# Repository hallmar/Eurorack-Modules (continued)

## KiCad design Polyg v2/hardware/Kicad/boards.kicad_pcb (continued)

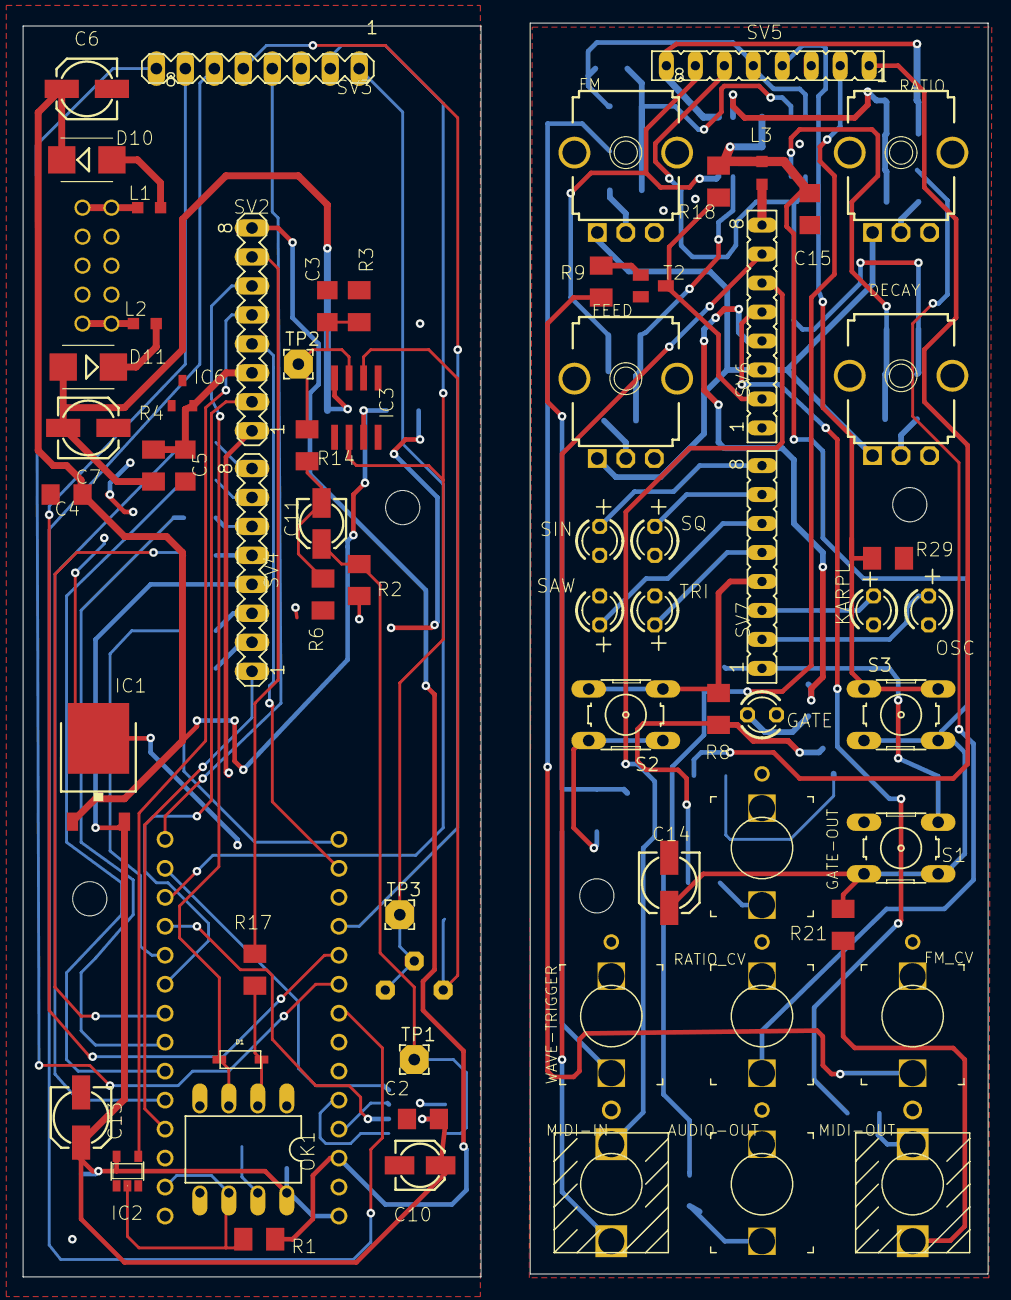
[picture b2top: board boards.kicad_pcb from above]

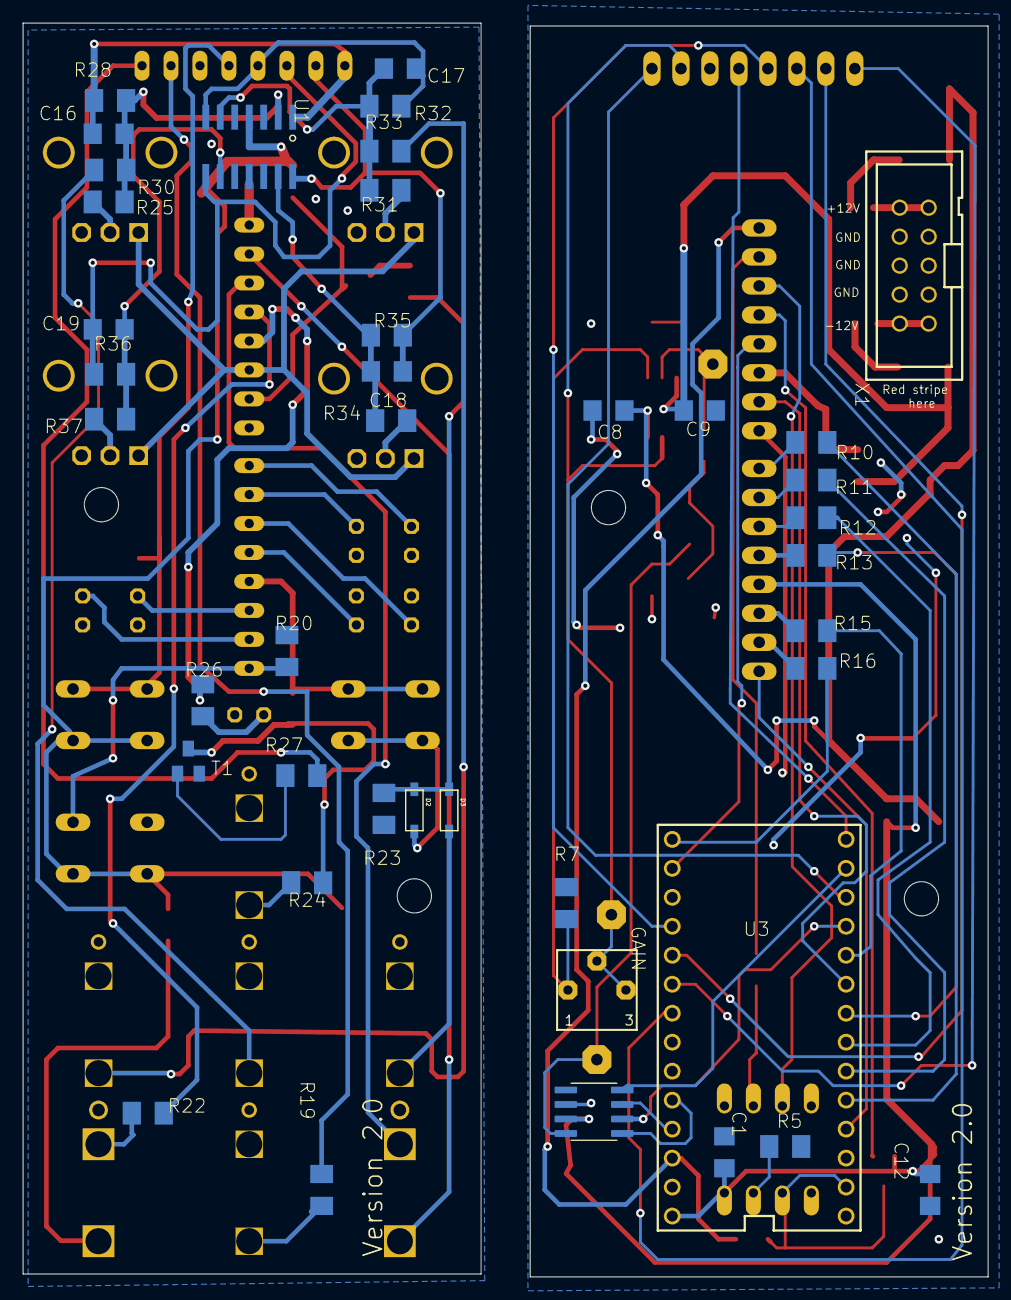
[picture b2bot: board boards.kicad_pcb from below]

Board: 2 copper layers, 84.6 x 109.9 mm, 110 parts (41 on the bottom side), 91 nets.

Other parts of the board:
@HOLE0, @HOLE1, @HOLE2, @HOLE3: (no value)

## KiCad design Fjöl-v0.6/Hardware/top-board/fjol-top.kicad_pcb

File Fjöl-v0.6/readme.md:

# Fjöl 4-Voice Midi synth, THIS IS A DEPRECATED PROJECT AND I'M ONLY KEEPING THIS HERE FOR ARCHIVING PURPOSES

Small demo video with non working LED's: https://www.youtube.com/watch?v=nTqA_WNiwQo

Current hardware uses a high quality DAC(PCM5100) with 16bit/44.1kHz quality.

Fjöl is a 
4 voice polyphonic* Phase modulation synthesizer. Using only sine waves you can get the same sounds as an FM synthesizer.

* digital ladder LPF with resonance
* usb A host
* 3 operator Phase modulation with 3 algorithms(so far)
* two endless encoders with CV input for adjusting 8 different parameters 
* MIDI IN and MIDI THRU with type A midi minijacks as per MIDI standard.
* optional V/OCT and gate per voice expander also in the works
* i2c compatibility with Monome Teletype and Monome Crow (using Just Friends commands) is also on the roadmap
* possible Monome Grid compatibility on the roadmap

*(technically paraphonic since it's one filter for all voices)

Encoder parameters are:

* stereo spread of voices
* filter resonance
* filter envelope decay
* glide/portamento
* Operator 2 detune
* Operator 3 detune
* Operator 1 feedback (creates saw like wave)
* Operator 2 feedback

Potentiometers are:

* Operator 2 amplitude
* Operator 2 ratio
* Operator 3 amplitude
* Operator 3 ratio
* VCA Attack 
* VCA Release
* LPF frequency
* Filter envelope amplitude

Algorithms so far:

### Algo 1: 

OP2 -> OP1

OP3 -> OP1

### Algo 2:

OP3 -> OP2 -> OP1

### Algo 3:

OP3 -> OP1

OP2 -> OUT

## Designed With

* KiCAD
* Arduino IDE 
* Visual Studio Code
* Audio System Design Tool for Teensy Audio Library

## Versioning
* 0.6 - [Hardware] Original PCB
* 0.6 - [Software] Original software 
## Authors

* **Hallmar Gauti Halldórsson** (hardware and firmware)

## License
Hardware: CC BY-SA 4.0

Software: CC BY-SA 4.0

But if you want to sell or do something with the software or hardware then it'd be nice to include my name and link to my Github somewhere :)

## Acknowledgments

* All of Mutable Instruments designs have been an insparation and a solid reference for both analog and digital circuits.
https://github.com/pichenettes/eurorack

* The whole idea of a 4 voice poly synth was planted in my head after trying MakeSynthsNotWar's String Theory module.
https://makesynthsnotwar.com/modules/stringtheory/

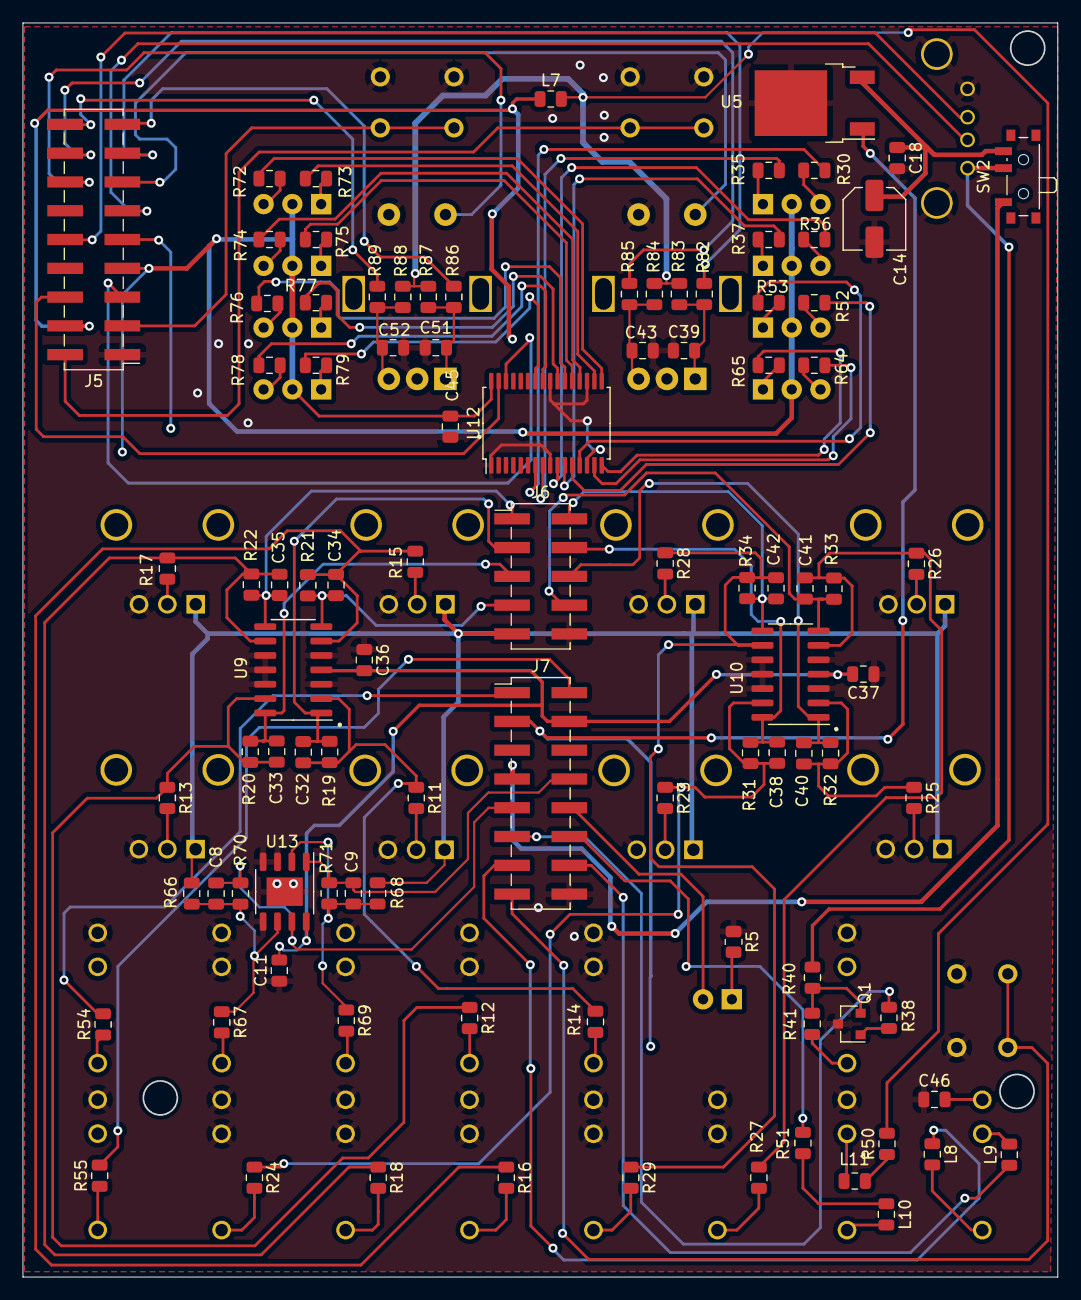
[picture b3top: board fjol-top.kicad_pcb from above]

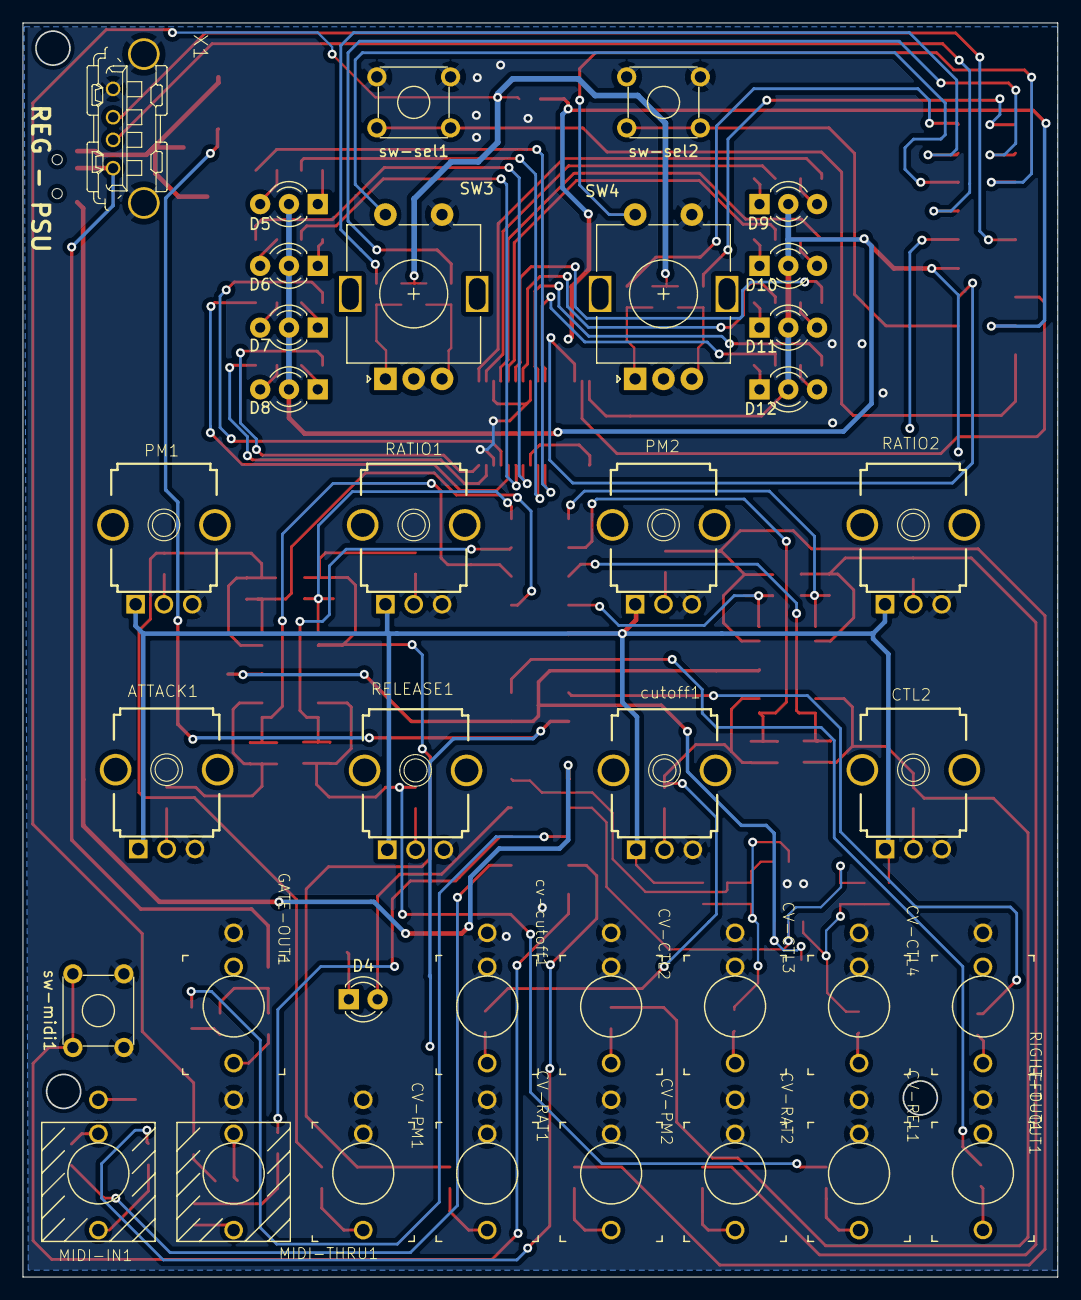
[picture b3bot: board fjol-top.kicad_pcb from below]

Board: 2 copper layers, 91.2 x 110.6 mm, 134 parts (37 on the bottom side), 116 nets.

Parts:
ATTACK1: 50k-lin; 9MM_SNAP-IN_POT
C8, C9, C32, C33, C34, C35, C38, C40, C41, C42: 1n; C_0805_2012Metric
C11, C18, C36, C37, C39, C43, C45, C46, C51, C52: 100n; C_0805_2012Metric
C14: 100u; C_Elec_5x5.8
CTL2: 50k-lin; 9MM_SNAP-IN_POT
CV-CTL2, CV-CTL3, CV-CTL4: THONKICONNNEW; WQP-PJ301M-12_JACK
CV-PM1, CV-PM2: THONKICONNNEW; WQP-PJ301M-12_JACK
CV-RAT1, CV-RAT2: THONKICONNNEW; WQP-PJ301M-12_JACK
CV-REL1: THONKICONNNEW; WQP-PJ301M-12_JACK
D4: LED; LED_D3.0mm
D5, D6, D7, D8, D9, D10, D11, D12: LED_Dual_KAK; LED_D3.0mm-3
GATE-OUT1: THONKICONNNEW; WQP-PJ301M-12_JACK
J5: Conn_01x18_Male; PinHeader_2x09_P2.54mm_Vertical_SMD
J6: Conn_01x10_Male; PinHeader_2x05_P2.54mm_Vertical_SMD
J7: Conn_01x16_Male; PinHeader_2x08_P2.54mm_Vertical_SMD
L7: BLM21PG221SN1D; L_0805_2012Metric
L8, L9, L10, L11: BLM21AG102SN1D; L_0805_2012Metric
LEFT-OUT1: THONKICONNNEW; WQP-PJ301M-12_JACK
MIDI-IN1: THONKI-STEREO; WQP-PJ366ST_JACK
MIDI-THRU1: THONKI-STEREO; WQP-PJ366ST_JACK
PM1, PM2: 50k-lin; 9MM_SNAP-IN_POT
Q1: BC847; SOT-23
R5, R38, R41, R54, R55: 1k; R_0805_2012Metric
R11, R13, R15, R17, R23, R25, R26, R28, R66, R68: 200k; R_0805_2012Metric
R12, R14, R16, R18, R24, R27, R29, R67, R69: 100k; R_0805_2012Metric
R19, R20, R21, R22, R31, R32, R33, R34, R70, R71: 66.5k; R_0805_2012Metric
R30, R35, R36, R37, R52, R53, R64, R65, R72, R73, R74, R75, R76, R77, R78, R79: 100; R_0805_2012Metric
R40, R82, R83, R84, R85, R86, R87, R88, R89: 10k; R_0805_2012Metric
R50: 33; R_0805_2012Metric
R51: 10; R_0805_2012Metric
RATIO1, RATIO2: 50k-lin; 9MM_SNAP-IN_POT
RELEASE1: 50k-lin; 9MM_SNAP-IN_POT
RIGHT-OUT1: THONKICONNNEW; WQP-PJ301M-12_JACK
SW2: SW_SPDT; SW_SPDT_PCM12
SW3: ctl1; RotaryEncoder_Alps_EC11E-Switch_Vertical_H20mm
SW4: ctl2; RotaryEncoder_Alps_EC11E-Switch_Vertical_H20mm
U5: L7805; TO-252-2
U9, U10: MCP6004; SOIC-14_3.9x8.7mm_P1.27mm
U12: PCA9622; TSSOP-32_6.1x11mm_P0.65mm
U13: MCP6002; SOIC-8-1EP_3.9x4.9mm_P1.27mm_EP2.514x3.2mm
X1: KUSBVX
cutoff1: 50k-lin; 9MM_SNAP-IN_POT
cv-cutoff1: THONKICONNNEW; WQP-PJ301M-12_JACK
sw-midi1: SW_MEC_5G; SW_TH_Tactile_Omron_B3F-10xx
sw-sel1, sw-sel2: SW_MEC_5G; SW_TH_Tactile_Omron_B3F-10xx

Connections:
5V_USB: R40.2, SW2.2 (B), X1.1
+3.3VA_F: C11.2, C36.2, C37.2, J7.4, U9.4 (V+), U10.4 (V+), U13.8 (V+)
+3.3VP_F: C45.1, D5.2 (A), D6.2 (A), D7.2 (A), D8.2 (A), D9.2 (A), D10.2 (A), D11.2 (A), D12.2 (A), J5.7, U12.32 (VDD)
+3.3V_F: J5.4, L7.1
+3.3V_F1: L7.2, R50.2, R83.2, R84.2, R87.2, R88.2
+12V-F: J7.3, U5.1 (IN)
-10V_F: ATTACK1.1, CTL2.1, J6.9, PM1.1, PM2.1, R66.2, R68.2, RATIO1.1, RATIO2.1, RELEASE1.1, cutoff1.1
ATTACK_F: C40.1, J6.6, R32.1, U10.1
CONTROL1_CV_F: C9.1, J7.8, R71.1, U13.1
CONTROL2_CV_F: C8.1, J7.9, R70.1, U13.7
CONTROL3_F: C33.1, J6.5, R20.1, U9.14
D+_F: J5.10, X1.3
D-_F: J5.11, X1.2
GATE-F: J7.11, R38.2
GND: ATTACK1.3, C11.1, C14.2, C18.2, C36.1, C37.1, C39.1, C43.1, C45.2, C46.1, C51.1, C52.1, CTL2.3, CV-CTL2.P$2_SWITCH (SWITCH), CV-CTL2.P$3_SLEEVE (SLEEVE), CV-CTL3.P$2_SWITCH (SWITCH), CV-CTL3.P$3_SLEEVE (SLEEVE), CV-CTL4.P$2_SWITCH (SWITCH), CV-CTL4.P$3_SLEEVE (SLEEVE), CV-PM1.P$2_SWITCH (SWITCH), CV-PM1.P$3_SLEEVE (SLEEVE), CV-PM2.P$2_SWITCH (SWITCH), CV-PM2.P$3_SLEEVE (SLEEVE), CV-RAT1.P$2_SWITCH (SWITCH), CV-RAT1.P$3_SLEEVE (SLEEVE), CV-RAT2.P$2_SWITCH (SWITCH), CV-RAT2.P$3_SLEEVE (SLEEVE), CV-REL1.P$2_SWITCH (SWITCH), CV-REL1.P$3_SLEEVE (SLEEVE), GATE-OUT1.P$3_SLEEVE (SLEEVE), J5.1, J6.10, J7.16, LEFT-OUT1.P$3_SLEEVE (SLEEVE), MIDI-THRU1.P$3_SLEEVE (SLEEVE), PM1.3, PM2.3, Q1.3 (E), R5.1, RATIO1.3, RATIO2.3, RELEASE1.3, RIGHT-OUT1.P$3_SLEEVE (SLEEVE), SW3.C, SW3.S1, SW4.C, SW4.S1, U5.2 (GND), U9.3 (+), U9.5 (+), U9.10 (+), U9.11 (V-), U9.12 (+), U10.3 (+), U10.5 (+), U10.10 (+), U10.11 (V-), U10.12 (+), U12.1 (VSS), U12.9 (VSS), U12.14 (VSS), U12.19 (VSS), U12.24 (VSS), U13.3 (+), U13.4 (V-), U13.5 (+), U13.9 (V-), X1.4, X1.M1 (S1), X1.M2 (S2), cutoff1.3, cv-cutoff1.P$2_SWITCH (SWITCH), cv-cutoff1.P$3_SLEEVE (SLEEVE), sw-midi1.3 (B), sw-midi1.4 (B), sw-sel1.3 (B), sw-sel1.4 (B), sw-sel2.3 (B), sw-sel2.4 (B)
LEFT-OUT-F: J7.1, R54.2
MIDI-IN-L-F: J7.13, L8.1
MIDI-IN-R-F: J7.14, L9.1
MIDI-THRU-L-F: J7.12, R51.2
unnamed: ATTACK1.2, R25.2
unnamed: C8.2, R66.1, R67.1, R70.2, U13.6 (-)
unnamed: C9.2, R68.1, R69.1, R71.2, U13.2 (-)
unnamed: C14.1, C18.1, SW2.3 (C), U5.3 (OUT)
unnamed: C32.2, R11.1, R14.1, R19.2, U9.2 (-)
unnamed: C33.2, R12.1, R13.1, R20.2, U9.13 (-)
unnamed: C34.2, R15.1, R16.1, R21.2, U9.6 (-)
unnamed: C35.2, R17.1, R18.1, R22.2, U9.9 (-)
unnamed: C38.2, R23.1, R24.1, R31.2, U10.13 (-)
unnamed: C39.2, R82.1, R83.1, SW3.A
unnamed: C40.2, R25.1, R32.2, U10.2 (-)
unnamed: C41.2, R26.1, R27.1, R33.2, U10.6 (-)
unnamed: C42.2, R28.1, R29.1, R34.2, U10.9 (-)
unnamed: C43.2, R84.1, R85.2, SW3.B
unnamed: C46.2, MIDI-IN1.P$3_SLEEVE (SLEEVE)
unnamed: C51.2, R86.1, R87.1, SW4.A
unnamed: C52.2, R88.1, R89.2, SW4.B
unnamed: CTL2.2, R13.2
unnamed: CV-CTL2.P$1_TIP (TIP), R12.2
unnamed: CV-CTL3.P$1_TIP (TIP), R69.2
unnamed: CV-CTL4.P$1_TIP (TIP), R67.2
unnamed: CV-PM1.P$1_TIP (TIP), R27.2
unnamed: CV-PM2.P$1_TIP (TIP), R16.2
unnamed: CV-RAT1.P$1_TIP (TIP), R29.2
unnamed: CV-RAT2.P$1_TIP (TIP), R18.2
unnamed: CV-REL1.P$1_TIP (TIP), R24.2
unnamed: D5.1 (K1), R35.1
unnamed: D5.3 (K2), R30.1
unnamed: D6.1 (K1), R37.1
unnamed: D6.3 (K2), R36.1
unnamed: D7.1 (K1), R53.1
unnamed: D7.3 (K2), R52.1
unnamed: D8.1 (K1), R65.1
unnamed: D8.3 (K2), R64.1
unnamed: D9.1 (K1), R73.1
unnamed: D9.3 (K2), R72.1
unnamed: D10.1 (K1), R75.1
unnamed: D10.3 (K2), R74.1
unnamed: D11.1 (K1), R77.1
unnamed: D11.3 (K2), R76.1
unnamed: D12.1 (K1), R79.1
unnamed: D12.3 (K2), R78.1
unnamed: GATE-OUT1.P$1_TIP (TIP), R41.1
unnamed: L8.2, MIDI-IN1.P$1_TIP (LEFT)
unnamed: L9.2, MIDI-IN1.P$2_SWITCH (RIGHT)
unnamed: L10.1, R51.1
unnamed: L10.2, MIDI-THRU1.P$1_TIP (LEFT)
unnamed: L11.1, R50.1
unnamed: L11.2, MIDI-THRU1.P$2_SWITCH (RIGHT)
unnamed: LEFT-OUT1.P$1_TIP (TIP), R54.1
unnamed: PM1.2, R26.2
unnamed: PM2.2, R15.2
unnamed: Q1.1 (B), R38.1
unnamed: Q1.2 (C), R40.1, R41.2
unnamed: D4.1 (K), R5.2
unnamed: R11.2, cutoff1.2
unnamed: R14.2, cv-cutoff1.P$1_TIP (TIP)
unnamed: R17.2, RATIO2.2
unnamed: R23.2, RELEASE1.2
unnamed: R28.2, RATIO1.2
unnamed: R55.1, RIGHT-OUT1.P$1_TIP (TIP)
PM1_F: C41.1, J6.8, R33.1, U10.7
PM2_F: C34.1, J6.7, R21.1, U9.7
RATIO1_F: C42.1, J6.2, R34.1, U10.8
RATIO2_F: C35.1, J6.1, R22.1, U9.8
RELEASE_F: C38.1, J6.4, R31.1, U10.14
RIGHT-OUT-F: J7.2, R55.2
SCL_F: J5.5, U12.30 (SCL)
SDA_F: J5.6, U12.31 (SDA)
ctl1_enc_A_F: J5.15, R82.2
ctl1_enc_B_F: J5.16, R85.1
ctl1_sw_F: J5.13, SW3.S2
ctl2_enc_A_F: J5.17, R86.2
ctl2_enc_B_F: J5.18, R89.1
ctl2_sw_F: J5.14, SW4.S2
cutoff_f: C32.1, J6.3, R19.1, U9.1
euro-5V_f: J7.7, SW2.1 (A)
led1_g: R30.2, U12.7 (LED0)
led1_r: R35.2, U12.8 (LED1)
led2_g: R36.2, U12.10 (LED2)
led2_r: R37.2, U12.11 (LED3)
led3_g: R52.2, U12.12 (LED4)
led3_r: R53.2, U12.13 (LED5)
led4_g: R64.2, U12.15 (LED6)
led4_r: R65.2, U12.16 (LED7)
led5_g: R72.2, U12.17 (LED8)
led5_r: R73.2, U12.18 (LED9)
led6_g: R74.2, U12.20 (LED10)
led6_r: R75.2, U12.21 (LED11)
led7_g: R76.2, U12.22 (LED12)
led7_r: R77.2, U12.23 (LED13)
led8_g: R78.2, U12.25 (LED14)
led8_r: R79.2, U12.26 (LED15)
led_gate_f: D4.2 (A), J7.10
midi_sw-F: J7.15, sw-midi1.1 (A), sw-midi1.2 (A)
switch1_sw-F: J5.2, sw-sel1.1 (A), sw-sel1.2 (A)
switch2_sw-F: J5.3, sw-sel2.1 (A), sw-sel2.2 (A)

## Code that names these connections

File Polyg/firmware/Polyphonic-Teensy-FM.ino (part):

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
//----Outputs----------
const short gate_o = 10;
const short sin_led = 3;
const short sq_led = 4;
const short saw_led = 5;
const short tri_led = 6;
const short string_led = 8;
const short osc_led = 13;

//----Inputs-------------
const short waveshape = 7;
const short envelope = 12;
const short midi_learn = 2;
Bounce wavesh_but = Bounce();
Bounce envel_but = Bounce();
Bounce midilearn_but = Bounce();
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{
  
  AudioMemory(80);
  pinMode(sin_led, OUTPUT);
  pinMode(sq_led, OUTPUT);
  pinMode(saw_led, OUTPUT);
  pinMode(tri_led, OUTPUT);
  pinMode(string_led, OUTPUT);
  pinMode(osc_led, OUTPUT);
  pinMode(gate_o, OUTPUT);
  
  digitalWrite(sin_led, HIGH);
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  digitalWrite(string_led, LOW);
  digitalWrite(osc_led, HIGH);
  
  pinMode(waveshape, INPUT);
  pinMode(envelope, INPUT);
  pinMode(midi_learn, INPUT);
  
  wavesh_but.attach(waveshape);
  wavesh_but.interval(debounce);
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
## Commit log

2018-11-12 Create Polyg
2020-09-20 deleted badly designed polyg v1
2020-09-20 add images
2020-11-19 endurnefna möppu
2020-11-19 endurnefna pdf
2020-11-20 möppubreytingar
2020-11-29 setja inn ókláraða útgáfu af firmware og hardware
2020-11-30 breyta um mynd
2020-12-24 upload pdf
2020-12-25 breyta mynd
2020-12-25 uppfæra mynd
2021-01-19 upddate to KICAD
2021-01-19 updatepdf
2021-01-19 updatepdffolder
2021-02-19 update frontpanel
2023-01-03 change version
2023-01-03 put up new version of Fjöl on Github
2023-01-19 change folder name
